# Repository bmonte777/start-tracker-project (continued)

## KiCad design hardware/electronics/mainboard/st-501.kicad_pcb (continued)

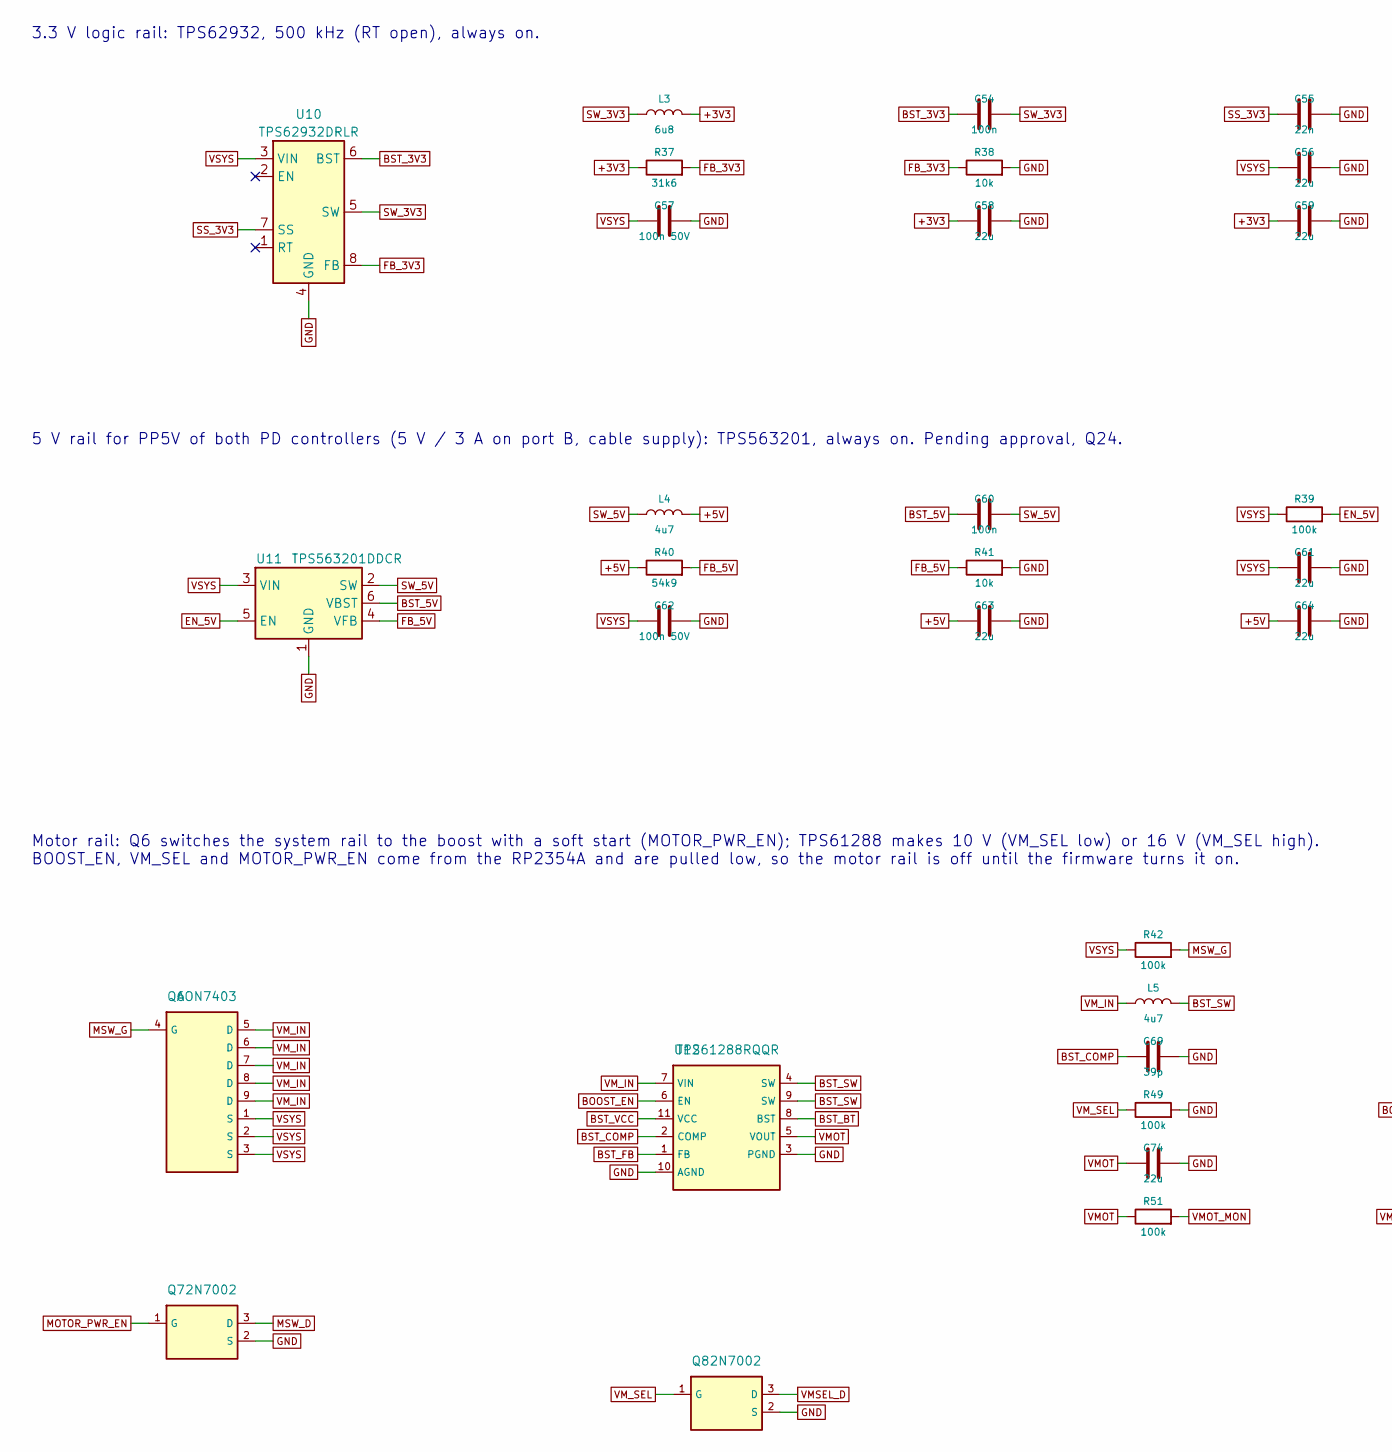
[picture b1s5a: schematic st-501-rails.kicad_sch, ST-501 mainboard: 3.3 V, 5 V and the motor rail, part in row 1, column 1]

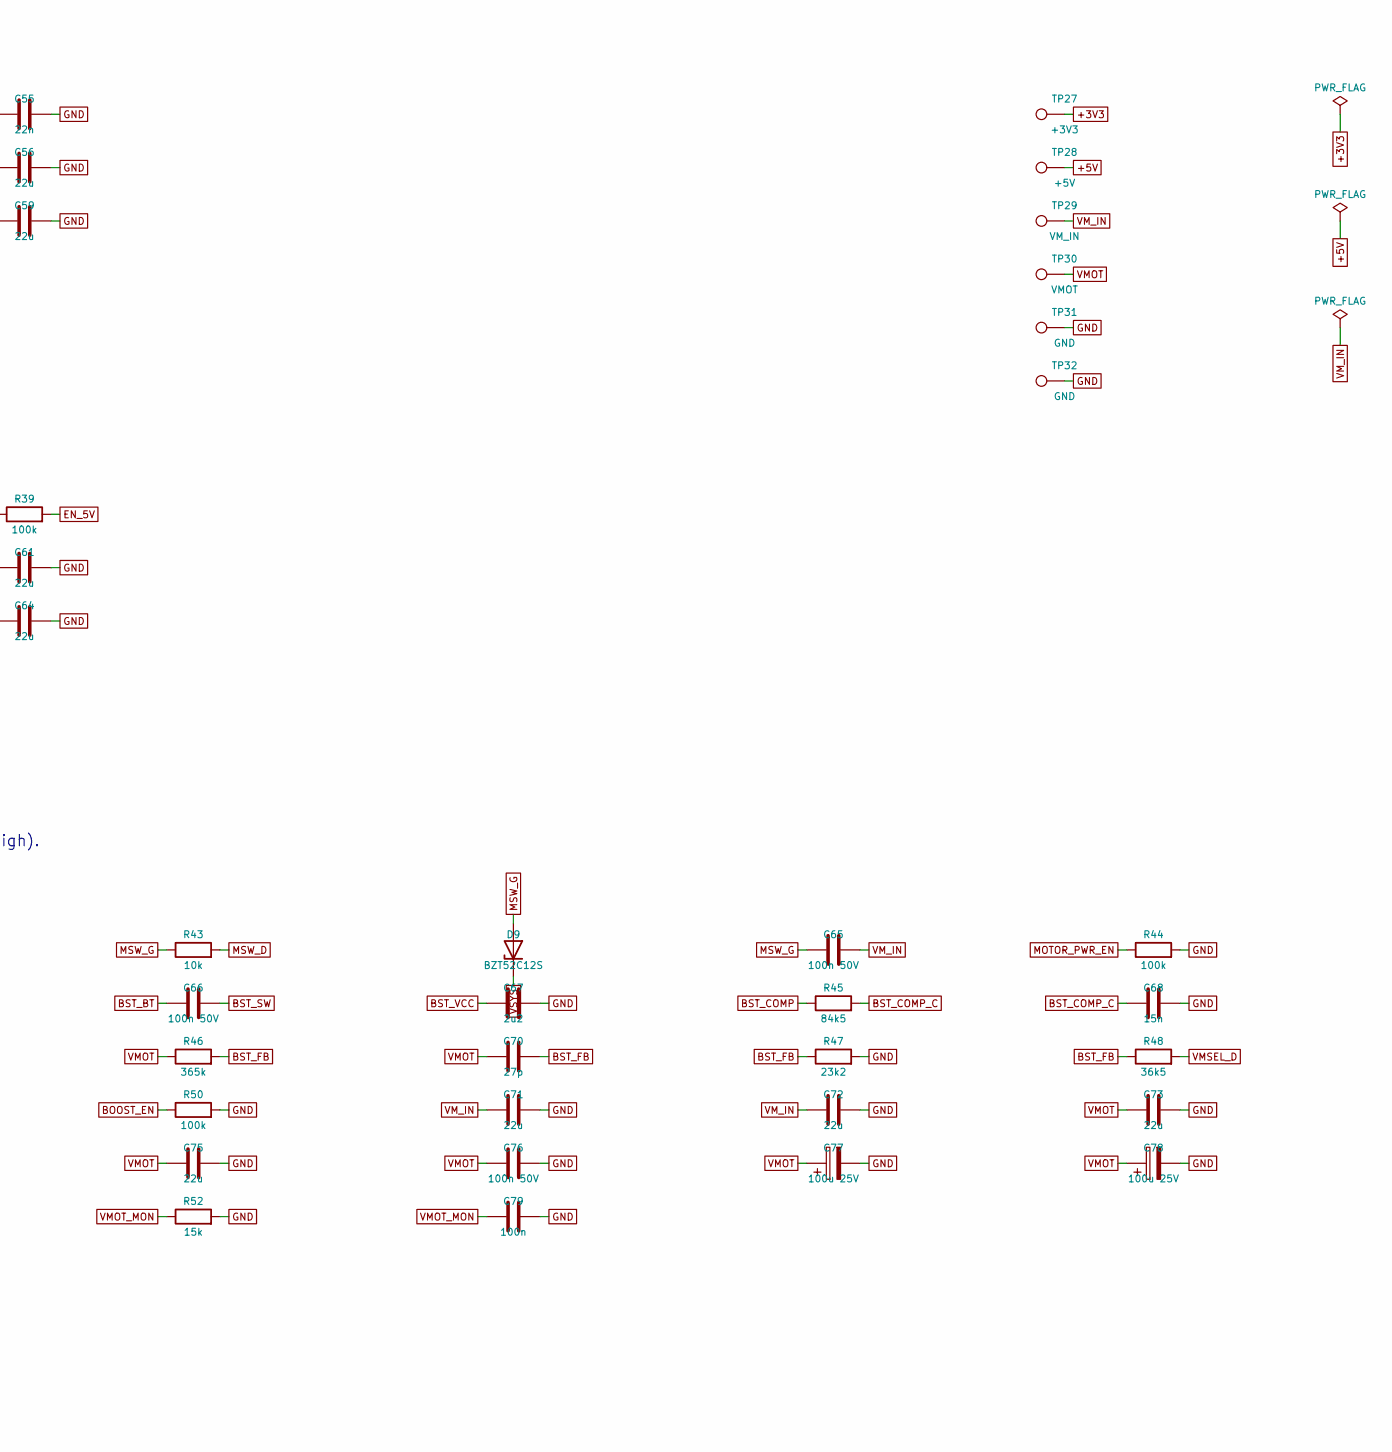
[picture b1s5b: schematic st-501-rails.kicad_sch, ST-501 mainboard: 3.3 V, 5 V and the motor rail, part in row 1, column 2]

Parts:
C54, C60, C79: 100n; C_0402_1005Metric; MPN CL05B104KO5NNNC; LCSC C1525
C55: 22n; C_0402_1005Metric; MPN CL05B223KB5NNNC; LCSC C1532
C56, C58, C59, C61, C63, C64, C71, C72, C73, C74, C75: 22u; C_0805_2012Metric; MPN CL21A226MAQNNNE; LCSC C45783
C57, C62, C65, C66, C76: 100n 50V; C_0402_1005Metric; MPN CL05B104KB54PNC; LCSC C307331
C67: 2u2; C_0603_1608Metric; MPN CL10A225KO8NNNC; LCSC C23630
C68: 15n; C_0402_1005Metric; MPN 15 nF X7R 50 V 0402
C69: 39p; C_0402_1005Metric; MPN 39 pF C0G 50 V 0402
C70: 27p; C_0402_1005Metric; MPN CL05C270JB5NNNC; LCSC C1557
C77, C78: 100u 25V; CP_Elec_6.3x7.7; MPN 100 uF 25 V polymer hybrid
D9: BZT52C12S; D_SOD-323; MPN BZT52C12S; LCSC C14643
L3: 6u8; L_Sunlord_SWPA5040S; MPN SWPA5040S6R8MT; LCSC C36411
L4, L5: 4u7; L_Sunlord_MWSA0603S; MPN MWSC0630H4R7MT; LCSC C2991788
Q6: AON7403; DFN-8-1EP_3x3mm_P0.65mm_EP1.55x2.4mm; MPN AON7403; LCSC C5310961
Q7, Q8: 2N7002; SOT-23; MPN 2N7002; LCSC C8545
R37: 31k6; R_0402_1005Metric; MPN RC0402FR-0731K6L; LCSC C276265
R38, R41, R43: 10k; R_0402_1005Metric; MPN 0402WGF1002TCE; LCSC C25744
R39, R42, R44, R49, R50, R51: 100k; R_0402_1005Metric; MPN 0402WGF1003TCE; LCSC C25741
R40: 54k9; R_0402_1005Metric; MPN RC0402FR-0754K9L
R45: 84k5; R_0402_1005Metric; MPN RC0402FR-0784K5L
R46: 365k; R_0402_1005Metric; MPN RC0402FR-07365KL
R47: 23k2; R_0402_1005Metric; MPN RC0402FR-0723K2L
R48: 36k5; R_0402_1005Metric; MPN RC0402FR-0736K5L
R52: 15k; R_0402_1005Metric; MPN 0402WGF1502TCE; LCSC C25756
TP27: +3V3; TestPoint_Pad_D1.0mm
TP28: +5V; TestPoint_Pad_D1.0mm
TP29: VM_IN; TestPoint_Pad_D1.0mm
TP30: VMOT; TestPoint_Pad_D1.0mm
TP31, TP32: GND; TestPoint_Pad_D1.0mm
U10: TPS62932DRLR; SOT-583-8; MPN TPS62932DRLR; LCSC C3032935
U11: TPS563201DDCR; TSOT-23-6; MPN TPS563201DDCR; LCSC C116592
U12: TPS61288RQQR; Texas_VQFN-HR-20_3x2.5mm_P0.5mm_RQQ0011A; MPN TPS61288RQQR; LCSC C5219223

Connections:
+3V3: C58.1, C59.1, L3.2, R37.1, TP27.1; also elsewhere on the board
+5V: C63.1, C64.1, L4.2, R40.1, TP28.1; also elsewhere on the board
BOOST_EN: R50.1, U12.6 (EN); also elsewhere on the board
BST_3V3: C54.1, U10.6 (BST)
BST_5V: C60.1, U11.6 (VBST)
BST_BT: C66.1, U12.8 (BST)
BST_COMP: C69.1, R45.1, U12.2 (COMP)
BST_COMP_C: C68.1, R45.2
BST_FB: C70.2, R46.2, R47.1, R48.1, U12.1 (FB)
BST_SW: C66.2, L5.2, U12.4 (SW), U12.9 (SW)
BST_VCC: C67.1, U12.11 (VCC)
EN_5V: R39.2, U11.5 (EN)
FB_3V3: R37.2, R38.1, U10.8 (FB)
FB_5V: R40.2, R41.1, U11.4 (VFB)
GND: C55.2, C56.2, C57.2, C58.2, C59.2, C61.2, C62.2, C63.2, C64.2, C67.2, C68.2, C69.2, C71.2, C72.2, C73.2, C74.2, C75.2, C76.2, C77.2, C78.2, C79.2, Q7.2 (S), Q8.2 (S), R38.2, R41.2, R44.2, R47.2, R49.2, R50.2, R52.2, TP31.1, TP32.1, U10.4 (GND), U11.1 (GND), U12.3 (PGND), U12.10 (AGND); also elsewhere on the board
MOTOR_PWR_EN: Q7.1 (G), R44.1; also elsewhere on the board
MSW_D: Q7.3 (D), R43.2
MSW_G: C65.1, D9.2 (A), Q6.4 (G), R42.2, R43.1
SS_3V3: C55.1, U10.7 (SS)
SW_3V3: C54.2, L3.1, U10.5 (SW)
SW_5V: C60.2, L4.1, U11.2 (SW)
VMOT: C70.1, C73.1, C74.1, C75.1, C76.1, C77.1, C78.1, R46.1, R51.1, TP30.1, U12.5 (VOUT); also elsewhere on the board
VMOT_MON: C79.1, R51.2, R52.1; also elsewhere on the board
VMSEL_D: Q8.3 (D), R48.2
VM_IN: C65.2, C71.1, C72.1, L5.1, Q6.5 (D), Q6.6 (D), Q6.7 (D), Q6.8 (D), Q6.9 (D), TP29.1, U12.7 (VIN)
VM_SEL: Q8.1 (G), R49.1; also elsewhere on the board
VSYS: C56.1, C57.1, C61.1, C62.1, D9.1 (K), Q6.1 (S), Q6.2 (S), Q6.3 (S), R39.1, R42.1, U10.3 (VIN), U11.3 (VIN); also elsewhere on the board

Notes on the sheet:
3.3 V logic rail: TPS62932, 500 kHz (RT open), always on.
5 V rail for PP5V of both PD controllers (5 V / 3 A on port B, cable supply): TPS563201, always on. Pending approval, Q24.
Motor rail: Q6 switches the system rail to the boost with a soft start (MOTOR_PWR_EN); TPS61288 makes 10 V (VM_SEL low) or 16 V (VM_SEL high). BOOST_EN, VM_SEL and MOTOR_PWR_EN come from the RP2354A and are pulled low, so the motor rail is off until the firmware turns it on.

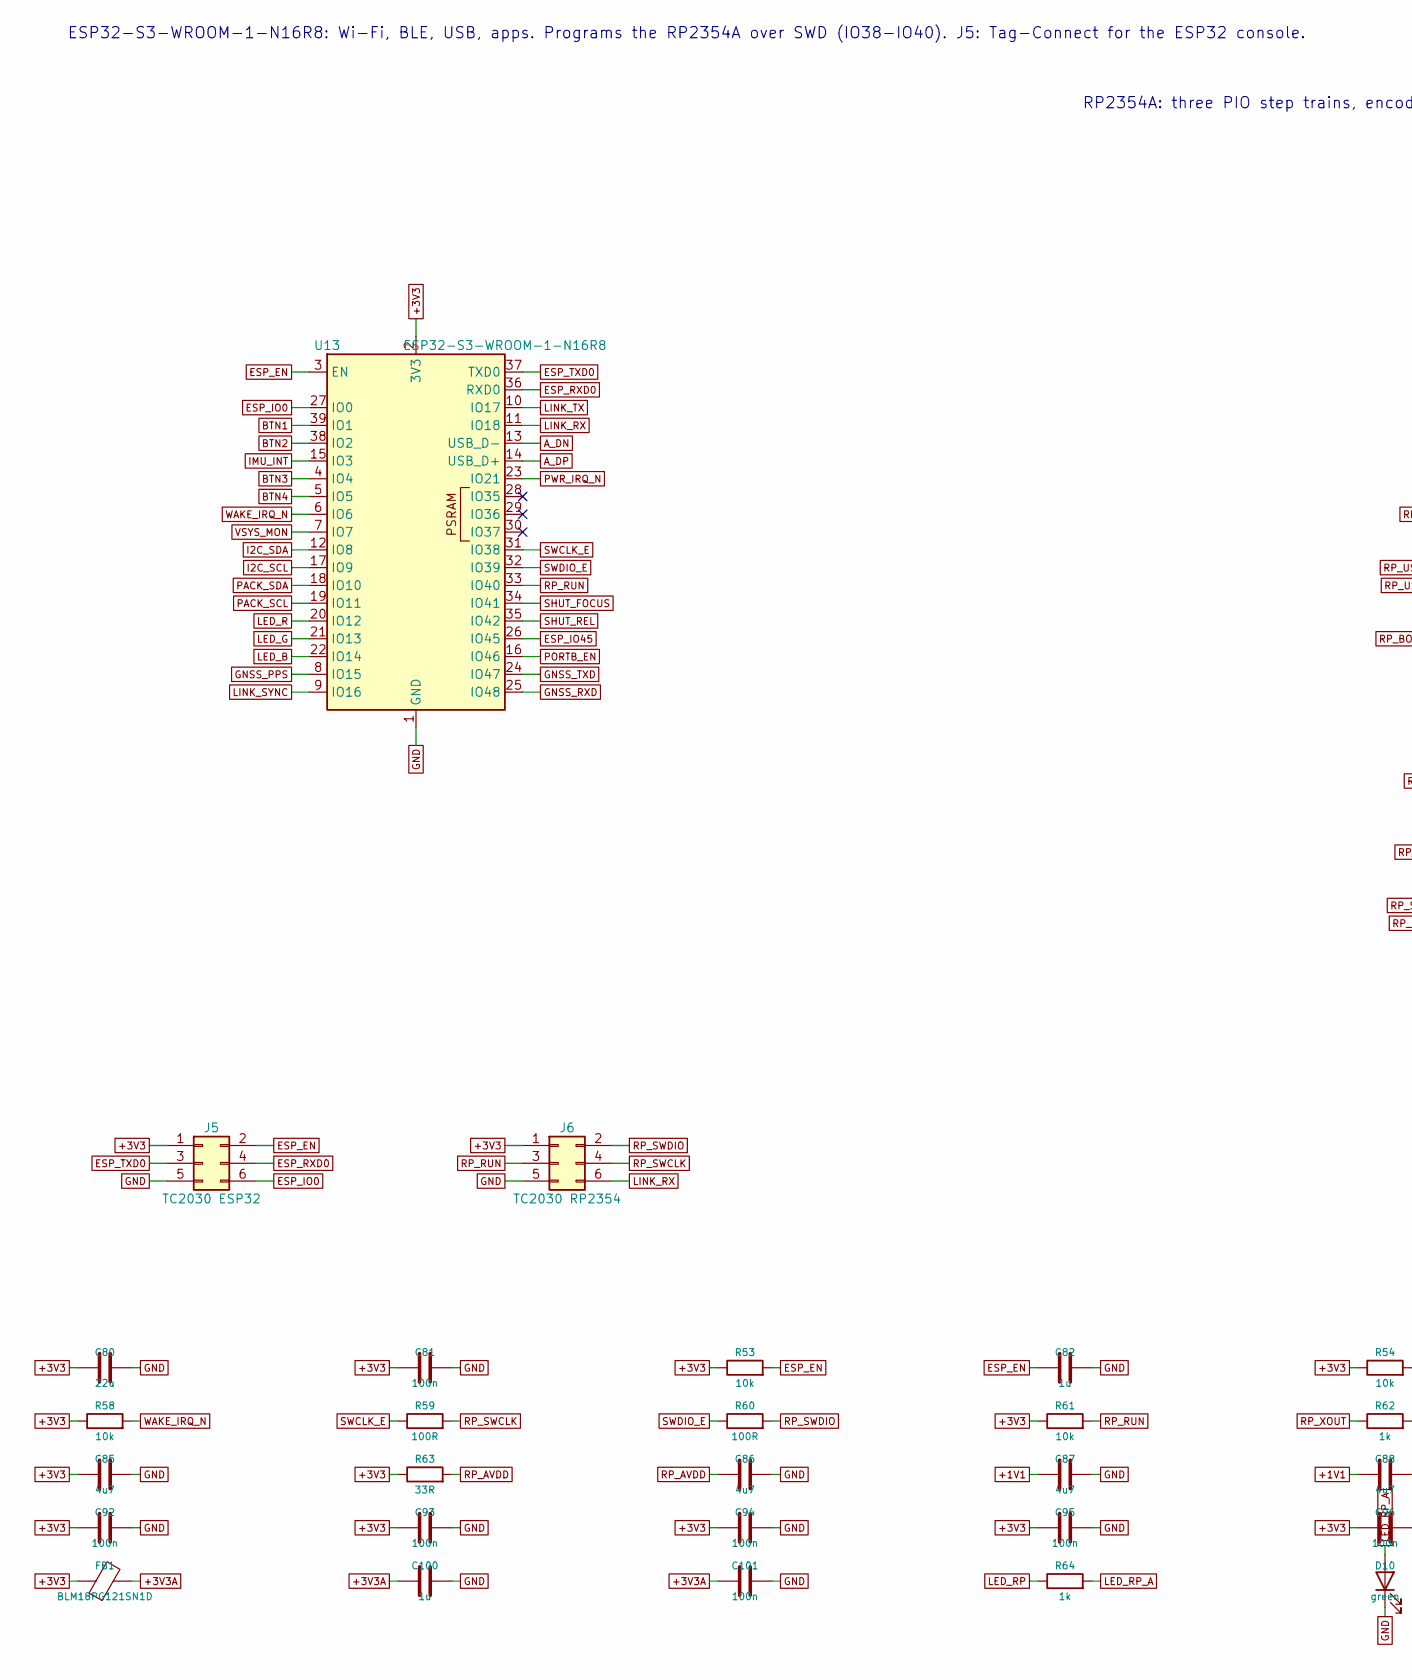
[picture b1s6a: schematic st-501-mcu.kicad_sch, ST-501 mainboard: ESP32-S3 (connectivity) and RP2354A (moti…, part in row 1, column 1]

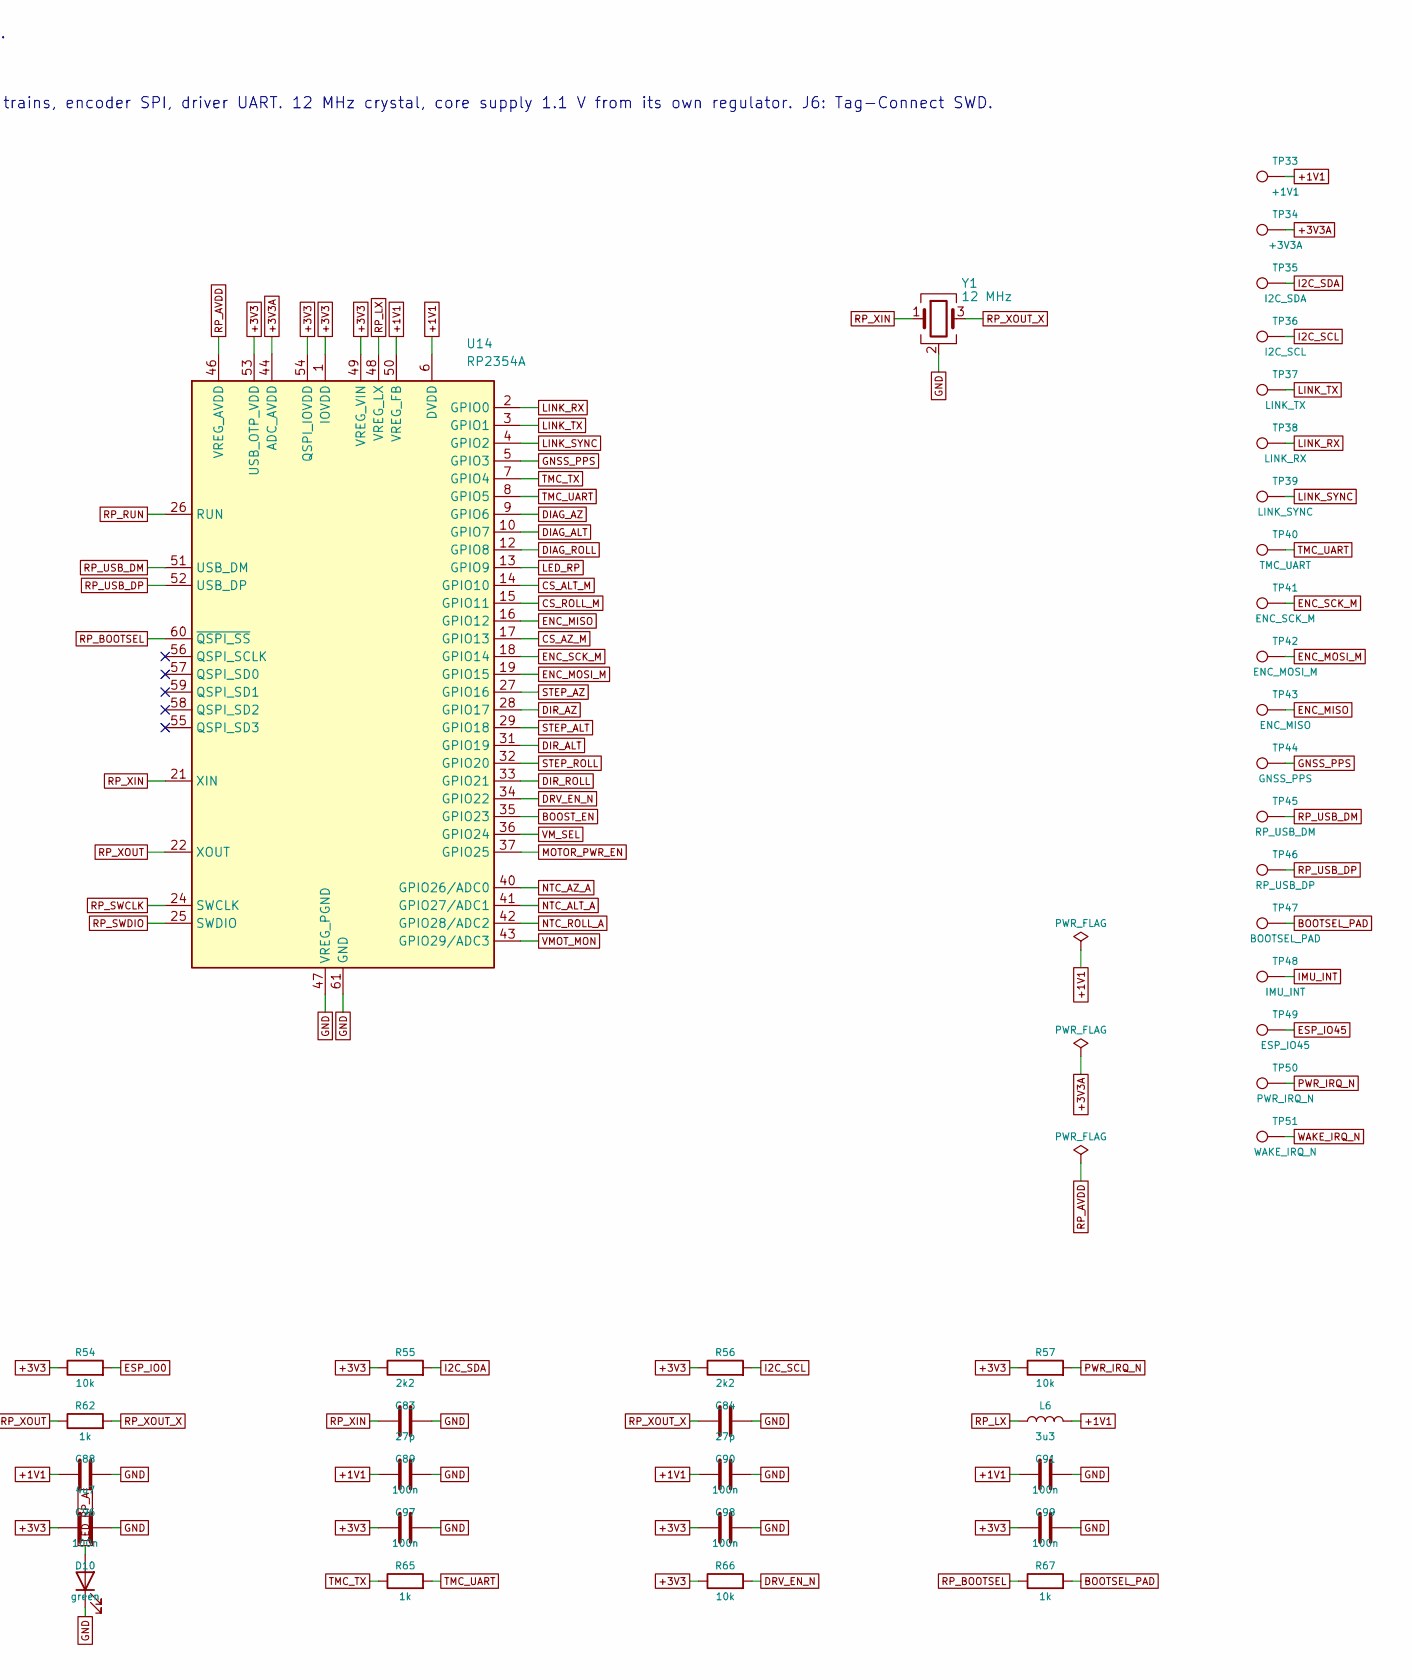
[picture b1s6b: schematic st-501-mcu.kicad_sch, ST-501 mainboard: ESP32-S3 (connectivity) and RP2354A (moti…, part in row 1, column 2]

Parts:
C80: 22u; C_0805_2012Metric; MPN CL21A226MAQNNNE; LCSC C45783
C81, C89, C90, C91, C92, C93, C94, C95, C96, C97, C98, C99, C101: 100n; C_0402_1005Metric; MPN CL05B104KO5NNNC; LCSC C1525
C82, C100: 1u; C_0402_1005Metric; MPN CL05A105KA5NQNC; LCSC C52923
C83, C84: 27p; C_0402_1005Metric; MPN CL05C270JB5NNNC; LCSC C1557
C85, C86, C87, C88: 4u7; C_0603_1608Metric; MPN CL10A475KO8NNNC; LCSC C19666
D10: green; LED_0603_1608Metric; MPN 19-217/GHC-YR1S2/3T; LCSC C72043
FB1: BLM18PG121SN1D; L_0603_1608Metric; MPN BLM18PG121SN1D; LCSC C14709
J5: TC2030 ESP32; Tag-Connect_TC2030-IDC-NL_2x03_P1.27mm_Vertical
J6: TC2030 RP2354; Tag-Connect_TC2030-IDC-NL_2x03_P1.27mm_Vertical
L6: 3u3; L_0805_2012Metric; MPN AOTA-B201610S3R3-101-T
R53, R54, R57, R58, R61, R66: 10k; R_0402_1005Metric; MPN 0402WGF1002TCE; LCSC C25744
R55, R56: 2k2; R_0402_1005Metric; MPN 0402WGF2201TCE; LCSC C25879
R59, R60: 100R; R_0402_1005Metric; MPN 0402WGF1000TCE; LCSC C25076
R62, R64, R65, R67: 1k; R_0402_1005Metric; MPN 0402WGF1001TCE; LCSC C11702
R63: 33R; R_0402_1005Metric; MPN 0402WGF330JTCE; LCSC C25105
TP33: +1V1; TestPoint_Pad_D1.0mm
TP34: +3V3A; TestPoint_Pad_D1.0mm
TP35: I2C_SDA; TestPoint_Pad_D1.0mm
TP36: I2C_SCL; TestPoint_Pad_D1.0mm
TP37: LINK_TX; TestPoint_Pad_D1.0mm
TP38: LINK_RX; TestPoint_Pad_D1.0mm
TP39: LINK_SYNC; TestPoint_Pad_D1.0mm
TP40: TMC_UART; TestPoint_Pad_D1.0mm
TP41: ENC_SCK_M; TestPoint_Pad_D1.0mm
TP42: ENC_MOSI_M; TestPoint_Pad_D1.0mm
TP43: ENC_MISO; TestPoint_Pad_D1.0mm
TP44: GNSS_PPS; TestPoint_Pad_D1.0mm
TP45: RP_USB_DM; TestPoint_Pad_D1.0mm
TP46: RP_USB_DP; TestPoint_Pad_D1.0mm
TP47: BOOTSEL_PAD; TestPoint_Pad_D1.0mm
TP48: IMU_INT; TestPoint_Pad_D1.0mm
TP49: ESP_IO45; TestPoint_Pad_D1.0mm
TP50: PWR_IRQ_N; TestPoint_Pad_D1.0mm
TP51: WAKE_IRQ_N; TestPoint_Pad_D1.0mm
U13: ESP32-S3-WROOM-1-N16R8; ESP32-S3-WROOM-1_BodyCourtyard; MPN ESP32-S3-WROOM-1-N16R8; LCSC C2913202
U14: RP2354A; QFN-60-1EP_7x7mm_P0.4mm_EP3.4x3.4mm; MPN RP2354A; LCSC C41378174
Y1: 12 MHz; Crystal_SMD_3225-4Pin_3.2x2.5mm; MPN X322512MSB4SI; LCSC C9002

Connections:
+1V1: C87.1, C88.1, C89.1, C90.1, C91.1, L6.2, TP33.1, U14.6 (DVDD), U14.23 (DVDD), U14.39 (DVDD), U14.50 (VREG_FB)
+3V3: C80.1, C81.1, C85.1, C92.1, C93.1, C94.1, C95.1, C96.1, C97.1, C98.1, C99.1, FB1.1, J5.1, J6.1, R53.1, R54.1, R55.1, R56.1, R57.1, R58.1, R61.1, R63.1, R66.1, U13.2 (3V3), U14.1 (IOVDD), U14.11 (IOVDD), U14.20 (IOVDD), U14.30 (IOVDD), U14.38 (IOVDD), U14.45 (IOVDD), U14.49 (VREG_VIN), U14.53 (USB_OTP_VDD), U14.54 (QSPI_IOVDD); also elsewhere on the board
+3V3A: C100.1, C101.1, FB1.2, TP34.1, U14.44 (ADC_AVDD); also elsewhere on the board
A_DN: U13.13 (USB_D-); also elsewhere on the board
A_DP: U13.14 (USB_D+); also elsewhere on the board
BOOST_EN: U14.35 (GPIO23); also elsewhere on the board
BOOTSEL_PAD: R67.2, TP47.1
BTN1: U13.39 (IO1); also elsewhere on the board
BTN2: U13.38 (IO2); also elsewhere on the board
BTN3: U13.4 (IO4); also elsewhere on the board
BTN4: U13.5 (IO5); also elsewhere on the board
CS_ALT_M: U14.14 (GPIO10); also elsewhere on the board
CS_AZ_M: U14.17 (GPIO13); also elsewhere on the board
CS_ROLL_M: U14.15 (GPIO11); also elsewhere on the board
DIAG_ALT: U14.10 (GPIO7); also elsewhere on the board
DIAG_AZ: U14.9 (GPIO6); also elsewhere on the board
DIAG_ROLL: U14.12 (GPIO8); also elsewhere on the board
DIR_ALT: U14.31 (GPIO19); also elsewhere on the board
DIR_AZ: U14.28 (GPIO17); also elsewhere on the board
DIR_ROLL: U14.33 (GPIO21); also elsewhere on the board
DRV_EN_N: R66.2, U14.34 (GPIO22); also elsewhere on the board
ENC_MISO: TP43.1, U14.16 (GPIO12); also elsewhere on the board
ENC_MOSI_M: TP42.1, U14.19 (GPIO15); also elsewhere on the board
ENC_SCK_M: TP41.1, U14.18 (GPIO14); also elsewhere on the board
ESP_EN: C82.1, J5.2, R53.2, U13.3 (EN)
ESP_IO0: J5.6, R54.2, U13.27 (IO0)
ESP_IO45: TP49.1, U13.26 (IO45)
ESP_RXD0: J5.4, U13.36 (RXD0)
ESP_TXD0: J5.3, U13.37 (TXD0)
GND: C80.2, C81.2, C82.2, C83.2, C84.2, C85.2, C86.2, C87.2, C88.2, C89.2, C90.2, C91.2, C92.2, C93.2, C94.2, C95.2, C96.2, C97.2, C98.2, C99.2, C100.2, C101.2, D10.1 (K), J5.5, J6.5, U13.1 (GND), U13.40 (GND), U13.41 (GND), U14.47 (VREG_PGND), U14.61 (GND), Y1.2 (G), Y1.4 (G); also elsewhere on the board
GNSS_PPS: TP44.1, U13.8 (IO15), U14.5 (GPIO3); also elsewhere on the board
GNSS_RXD: U13.25 (IO48); also elsewhere on the board
GNSS_TXD: U13.24 (IO47); also elsewhere on the board
I2C_SCL: R56.2, TP36.1, U13.17 (IO9); also elsewhere on the board
I2C_SDA: R55.2, TP35.1, U13.12 (IO8); also elsewhere on the board
IMU_INT: TP48.1, U13.15 (IO3); also elsewhere on the board
LED_B: U13.22 (IO14); also elsewhere on the board
LED_G: U13.21 (IO13); also elsewhere on the board
LED_R: U13.20 (IO12); also elsewhere on the board
LED_RP: R64.1, U14.13 (GPIO9)
LED_RP_A: D10.2 (A), R64.2
LINK_RX: J6.6, TP38.1, U13.11 (IO18), U14.2 (GPIO0)
LINK_SYNC: TP39.1, U13.9 (IO16), U14.4 (GPIO2)
LINK_TX: TP37.1, U13.10 (IO17), U14.3 (GPIO1)
MOTOR_PWR_EN: U14.37 (GPIO25); also elsewhere on the board
NTC_ALT_A: U14.41 (GPIO27/ADC1); also elsewhere on the board
NTC_AZ_A: U14.40 (GPIO26/ADC0); also elsewhere on the board
NTC_ROLL_A: U14.42 (GPIO28/ADC2); also elsewhere on the board
PACK_SCL: U13.19 (IO11); also elsewhere on the board
PACK_SDA: U13.18 (IO10); also elsewhere on the board
PORTB_EN: U13.16 (IO46); also elsewhere on the board
PWR_IRQ_N: R57.2, TP50.1, U13.23 (IO21); also elsewhere on the board
RP_AVDD: C86.1, R63.2, U14.46 (VREG_AVDD)
RP_BOOTSEL: R67.1, U14.60 (~QSPI_SS)
RP_LX: L6.1, U14.48 (VREG_LX)
RP_RUN: J6.3, R61.2, U13.33 (IO40), U14.26 (RUN)
RP_SWCLK: J6.4, R59.2, U14.24 (SWCLK)
RP_SWDIO: J6.2, R60.2, U14.25 (SWDIO)
RP_USB_DM: TP45.1, U14.51 (USB_DM)
RP_USB_DP: TP46.1, U14.52 (USB_DP)
RP_XIN: C83.1, U14.21 (XIN), Y1.1
RP_XOUT: R62.1, U14.22 (XOUT)
RP_XOUT_X: C84.1, R62.2, Y1.3
SHUT_FOCUS: U13.34 (IO41); also elsewhere on the board
SHUT_REL: U13.35 (IO42); also elsewhere on the board
STEP_ALT: U14.29 (GPIO18); also elsewhere on the board
STEP_AZ: U14.27 (GPIO16); also elsewhere on the board
STEP_ROLL: U14.32 (GPIO20); also elsewhere on the board
SWCLK_E: R59.1, U13.31 (IO38)
SWDIO_E: R60.1, U13.32 (IO39)
TMC_TX: R65.1, U14.7 (GPIO4)
TMC_UART: R65.2, TP40.1, U14.8 (GPIO5); also elsewhere on the board
VMOT_MON: U14.43 (GPIO29/ADC3); also elsewhere on the board
VM_SEL: U14.36 (GPIO24); also elsewhere on the board
VSYS_MON: U13.7 (IO7); also elsewhere on the board
WAKE_IRQ_N: R58.2, TP51.1, U13.6 (IO6); also elsewhere on the board

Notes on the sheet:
ESP32-S3-WROOM-1-N16R8: Wi-Fi, BLE, USB, apps. Programs the RP2354A over SWD (IO38-IO40). J5: Tag-Connect for the ESP32 console.
RP2354A: three PIO step trains, encoder SPI, driver UART. 12 MHz crystal, core supply 1.1 V from its own regulator. J6: Tag-Connect SWD.
